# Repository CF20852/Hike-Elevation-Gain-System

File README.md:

# Hike Elevation Gain System

## :construction: Still! UNDER CONSTRUCTION :construction:
There's just another week's worth of work to do, and there always will be.
## Description
This tool uses a microcomputer connected to a GPS receiver and a barometric pressure sensor to record timestamped hike latitude, longitude, and both GPS and barometric elevation data, and a macro-enabled Excel workbook that processes the recorded data to calculate an accurate elevation gain value for a hike.  The workbook VBA macros can also generate a Keyhole Markup Language (.kml) file that can be used to plot the hike route using mapping software, and calculate the total distance of the hike and the distance from the start to various landmarks along the way.

I developed this tool mainly due to frustration with the wide range of elevation gains reported by various sources, including MapMyHike, Google Maps, Google Earth, and Global Mapper.  Google Maps and Google Earth seemed to report more elevation gain than MapMyHike, and Google Earth and Global Mapper (both of which use, or can be configured to use, the Shuttle Radar Topography Mission [SRTM] terrain elevation data) seemed to be in some agreement.

The tool is a system comprising a recording component and a processing component.  The recording component uses an [Arduino](https://www.arduino.cc/en/Guide/Introduction) (or [Arduino-like](http://wiki.microduinoinc.com/Microduino_Series)) hardware platform that incorporates a GPS receiver such as a u-Blox NEO-6M or NEO-M8N to measure and record GPS time, latitude, longitude, and elevation, and a Bosch BMP180/BMP280 temperature and pressure sensor to measure and record the barometric pressure.  For information on the Arduino platform, visit the [Arduino website](https://www.arduino.cc).  For information on the u-Blox GPS receivers, visit the [u-Blox Positioning Chips and Modules website](https://www.u-blox.com/en/positioning-chips-and-modules).  For information on the Bosch pressure sensors, visit the [Bosch Sensortec website](https://www.bosch-sensortec.com/bst/products/environmental/barometric_pressure_sensors/overview_barometricpressuresensors).

The processing component consists of a macro-enabled Excel workbook that processes the recorded data.  There are four main steps in the elevation data processing:
* Correcting the barometric altimeter data, using altimeter setting data from a local airport.  This is what aircraft pilots use to ensure that they have the correct altitude information for the local area;
* Further correcting the barometric altimeter data, using terrain elevation data, which helps remove any constant bias in the barometric elevation data;
* Filtering (smoothing) and plotting the elevation data; and 
* Computing hike elevation gain/loss statistics.

More specifically, processing the hike elevation data includes the following steps:
* Compute some basic statistics of the hike, which include:
  * Start and end time
  * Average latitude and longitude
* Get the Meteorological Terminal Aviation Routine Weather Report (METAR) data for the airport nearest the hike site from before the beginning of the hike until after the end of the hike, using an [API](https://www.aviationweather.gov/help/webservice?page=metarjson) from [NOAA's Aviation Weather Center](https://aviationweather.gov/metar) that returns data in JSON (JavaScript Object Notation) format.  This gives us the local barometric altimeter setting that aircraft pilots use to set their altimeters to indicate the correct altitude, regardless of the local barometric pressure (within reasonable limits).
* Interpolate the METAR altimeter setting data between METAR sample times for each hike data recording sample time.
* Use the interpolated altimeter setting data to correct the measured barometric-pressure-based elevation data.
* Get the Google Maps elevation data corresponding to the latitude/longitude coordinates, using a [Google Maps API](https://developers.google.com/maps/) that returns data in JSON format.  This gives us (I think) the SRTM elevation data.
* Further correct the recorded barometric elevation data by applying a 1st order correction based on the Google Maps elevation data, to correct any constant bias in the barometric pressure data.  This is done using the Excel Solver add-in to calculate a constant barometric pressure offset value that minimizes the sum of the squared differences between the barometric elevation value and the Google Maps elevation value at each hike data recording sample time.
* Filter the GPS, barometric, and Google Maps elevation data using an [infinite-impulse-response (IIR) filter](https://en.wikipedia.org/wiki/Infinite_impulse_response), the development of which has been facilitated by a [tool](http://www-users.cs.york.ac.uk/~fisher/mkfilter/trad.html) developed by Tony Fisher (who is, unfortunately, deceased).
* Compute and display the hike elevation gain and loss from GPS elevation, barometric elevation, and Google Maps elevation.
* Plot (graph) the data.

My initial findings, based on data from 4-5 hikes, are that the barometric elevation data (once calibrated) are probably more realistic and less "noisy" than the measured GPS elevation data and the Google Maps elevation data.  An additional finding, based on experiments with a counterfeit of a u-Blox NEO-6M receiver, is that some GPS receivers (such as the genuine u-Blox receiver) provide much more accurate results than others (such as the Chinese counterfeit of a u-Blox NEO-6M receiver apparently manufactured by Hangzhou ZhongKe Microelectronics CO., Ltd).

## Installation
### Arduino (like) Code
I've posted three versions of the Arduino (or Arduino-like) code.  These three versions are posted here as Arduino sketchbook (not sketch) folders.  All of them use [William Greiman's SdFat library, which can be obtained at this link](https://github.com/greiman/SdFat).  In addition, they use customized versions of [SlashDevin's NeoGPS library](https://github.com/SlashDevin/NeoGPS), which I placed in the libraries folder inside the Arduino sketchbook folder for each version:
    - A version that runs on a Microduino Core+ with the Microduino GPS, Motion, SD, and USBTTL modules, which requires you to install the Arduino for Microduino Integrated Development Environment (IDE) from [the Microduino download site](https://microduinoinc.com/download/).  This IDE includes libraries for the Microduino Motion (\_06_m_Module_Motion), module, which I use, and GPS module (\_06_m_Module_GPS), which I don't use, except for testing the hardware configuration.  For the GPS receiver, I use SlashDevin's NeoGPS library, with some customization in the header files.  Please refer to the NEO-6M Setup.docx document for explanation of the customization.  The Core+ gives you two hardware serial ports.
    - A version that runs on an Arduino Uno with a shield containing a Chinese counterfeit of a u-Blox NEO-6M GPS receiver, which does not implement the u-Blox protocol, and a microSD card socket, and an [Adafruit BMP280 Barometric Pressure + Temperature Sensor Breakout](https://learn.adafruit.com/adafruit-bmp280-barometric-pressure-plus-temperature-sensor-breakout) that I attached and wired onto the shield, connecting SDA on the BMP280 breakout to A4 (SDA) on the Arduino and SCL on the BMP280 breakout to A5 (SCL) on the Arduino.  For this version, I have used SlashDevin's NeoGPS library with some customization in the header files, and the Adafruit BMP280 library.  I found a Chinese-language protocol specification for the Chinese GPS module labeled as a u-blox NEO-6M at [Hangzhou Zhongke Microelectronics Co., Ltd.](http://www.icofchina.com/d/file/xiazai/2017-05-02/ea0cdd3d81eeebcc657b5dbca80925ee.pdf) and translated it to English (with some expected formatting issues) using an [online document translator](https://www.onlinedoctranslator.com/en/translate-chinese-(simplified)-to-english_zh-CN_en), which worked better than expected.  I put a copy of the translated document in the sketchbook folder for this version.  The Arduino Uno only gives you one hardware serial port, tied to the USB port, so this version uses SlashDevin's NeoSWSerial library to communicate with the GPS module.
    - A version that runs on an Arduino Uno with a [DuinoPeak shield](http://duinopeak.com/index.php?route=product/product&product_id=112) containing a u-Blox NEO-N8M GPS receiver and a microSD card socket, and an [Adafruit BMP280 Barometric Pressure + Temperature Sensor Breakout](https://learn.adafruit.com/adafruit-bmp280-barometric-pressure-plus-temperature-sensor-breakout) that I attached and wired onto the shield, connecting SDA on the BMP280 breakout to A4 (SDA) on the Arduino and SCL on the BMP280 breakout to A5 (SCL) on the Arduino.  I used SlashDevin's NeoGPS library with customized header files and the Adafruit BMP280 library for this version also.
1.  Configure your hardware according to one of the options above.
2.  Download the corresponding sketchbook folder.
3.  In the Arduino IDE, go to File... Preferences... Sketchbook location and set the sketchbook location to the location of the sketchbook folder corresponding to the hardware configuration you chose.  See the notes on Arduino library usage below for an explanation of why I do it this way.
4.  Compile and upload the sketch to your Arduino or Microduino.
#### Some notes on Arduino library usage
When I first started developing the three hardware variants of this project, I put all of the necessary libraries in C:\Users\username\My Documents\Arduino\libraries, where my sketchbook folder was C:\Users\username\My Documents\Arduino.  That was OK for the barometric pressure sensor, because I could use one library for the BMP180 and another library for the BMP280, with no customization required.  But the NeoGPS library is highly configurable via multiple header files for different protocol types (e.g., NMEA vs proprietary), variations on what NMEA sentences different receivers put out, and what information you want out of those sentences (e.g., if you don't need speed and heading, you can configure the library to not parse them, thus saving processing time and memory).  The NeoGPS library has a a src folder containing NMEA sentence processing .h and .cpp files, and subfolder under src called ublox, which contains .h and .cpp files for handling the u-blox proprietary GPS receiver protocol.  In addition, using an Arduino Uno, which only has one hardware serial port, you have a specific GPS serial port configuration, but with the Microduino Core+, you have a second hardware serial port that you can use, which requires a different GPSPort.h configuration in NeoGPS.  So I started out creating different versions of the various NeoGPS header files with different names for the different configurations.  This (IMO) was a really bad idea, because if I update the NeoGPS library, the Arduino library manager replaces the existing library folder with the updated library folder, thus wiping out any custom header files I created.  (Hooray for daily backups!)  Moreover, it starts to get ugly (inelegant) fast.

After some research, I learned that the Arduino IDE looks for libraries in several places (the following is Windows specific):  (1) the libraries folder in your sketchbook, e.g. C:\Users\username\My Documents\Arduino\libraries; (2) in the libraries folder of the Arduino IDE installation folder, e.g. C:\Program Files (x86)\Arduino\libraries; (3) in the folders below C:\Program Files (x86)\Arduino\hardware, e.g., C:\Program Files (x86)\Arduino\hardware\arduino\avr\libraries; and (4) in your sketch folder.  If you want to include a library in one of the first three places, you enclose the appropriate header file name in angle brackets (<>), e.g.,

`#include <SomeLib.h>`,

and if you want to include a library in your sketch (not sketchbook) folder, you enclose the header file name in double quotes, e.g.

`#include "MyLib.h"`.

I'm told that if you use the latter syntax, if the Arduino IDE doesn't find the library source file in your sketch folder, it will look in the places listed above for the angle bracket syntax.

To be able to have several different configurations of the NeoGPS library, as well as other libraries including Adafruit_BMP280_Library or Adafruit_BMP085_Library, NeoSWSerial (if using an Arduino Uno, not needed for a Microduino Core+), PString, and SDFat, the solution I eventually settled on is to have a different sketchbook folder for each configuration, containing a libraries folder and a sketch folder.  I have a copy of the each of the required libraries that are normally stored in the Arduino sketchbook folder in the libraries folder of the hardware-configuration-specific sketchbook folders.  The main disadvantage of this approach (in addition to multiple copies of libraries that you may need to update) is that you have to remember to point the Arduino IDE to the correct sketchbook.  You can easily change the sketchbook folder that the Arduino IDE uses under File... Preferences... Sketchbook location in the Arduino IDE (I'm using version 1.8.5 right now).

Another thing I learned is that if a library has at least one subfolder containing additional source code (.h and/or .cpp) files, all of the source code files must be within a src folder inside the library folder, or the IDE won't find the source code files within the subfolder.  An exception to this src folder requirement may be if the subfolder is named "utility".  See the Arduino IDE 1.5: Library specfication, under the Layout of folders and files heading.  I quote:  

>The source code found in src folder and all its subfolders is compiled and linked in the user's sketch. Only the src folder is added to the include search path (both when compiling the sketch and the library). When the user imports a library into their sketch (from the "Tools > Import Library" menu), an #include statement will be added for all header (.h) files in the src/ directory (but not its subfolders). As a result, these header files form something of a de facto interface to your library; in general, the only header files in the root src/ folder should be those that you want to expose to the user's sketch and plan to maintain compatibility with in future versions of the library. Place internal header files in a subfolder of the src/ folder.

>For backward compatibility with Arduino 1.0.x, the library author may opt to place source code into the root folder, instead of the folder called src. In this case the 1.0 library format is applied and the source code is searched from the library root folder and the utility folder...

I hope this explanation helps someone avoid wasting the amount of time I did in making my project work and look (I hope) at least a bit elegant.

### Excel Workbook
1.  Of course, you'll need Microsoft Excel to use the Excel macro-enabled workbook.  I used Excel 2016.

2.  I was very happy to find an Excel Visual Basic for Applications (VBA) JSON parser at https://github.com/VBA-tools/VBA-JSON.  It's always nice to find some giants who are willing to let you stand on their shoulders.  I just downloaded JsonConverter.bas from [that site](https://github.com/VBA-tools/VBA-JSON) and imported it into my Visual Basic code as a module.

3.  My Excel macro-enabled workbook also uses the Solver Add-in.  If you haven't already enabled it in your copy of Excel, you'll need to do so.  In my version (2016) of Excel, that's done by going to File... Options... Add-ins... Manage Excel Add-ins... Go, and then checking the Solver box and clicking OK.  Depending on which version of Excel you have, your approach may differ.

4.  Download and open the workbook from this page.  When you open the spreadsheet in Excel, you'll probably have to OK enabling macros.

5.  I hike mainly in Arizona, Maryland, Pennsylvania, Virginia, and West Virginia, so those are the states for which I've included airports that report METAR data in the Airports tab of the workbook.  If you live somewhere else, you'll need to download the airports for your area from the [ADDS Station Table](https://www.aviationweather.gov/docs/metar/stations.txt).  Only include the stations that have a "X" in the "M" column of the table (column 63).  Just append them to the bottom of the Airports sheet below the other airports.

## Operation
### Arduino
There's not much to it.  The way it stands right now, if you plug a [well-formatted SD card](https://www.sdcard.org/downloads/formatter_4/) into the recorder, with less than 99 HikeLgxx.csv files (where xx = 0-99) on it, and apply power, it'll create a new HikeLgxx.csv file with the next available number and start recording every 2 seconds as soon as the GPS receiver starts outputting messages.
### Excel Workbook
#### Elevation Gain Calculations
This is a lot more complicated than the Arduino part, given the current state of the "art"...
1.  Ensure that you have an internet connection, because the macros have to retrieve data using the Aviation Weather Center METAR API and the Google Maps elevation data API;
2.  On the Control sheet of the Excel workbook, enter the following data:
    - Your Google Maps API key, which you can obtain from [this website](https://developers.google.com/maps/documentation/elevation/start), in cell B7;
    - Date of the hike, in YYYY-MM-DD or MM/DD/YYYY format, in cell B14.
    - As far as the other cells on the Control sheet are concerned, you should either not mess with them or they will be automagically filled in by the macros.
2.  Open the .csv file recorded by the Microduino or Arduino as an Excel spreadsheet;
3.  Delete everything in the Data sheet of the Excel workbook below the header row, which is row 1 i.e., delete everything in row 2 and below;
4.  Copy the UTC time, latitude and longitude (+/-DD.DDDDD format), GPS elevation (feet), temperature (degrees C), pressure (HPa), baro elevation (feet), number of satellites, HDOP, and VDOP data from the appropriate Hikelgxx.csv file to the Data sheet starting in Row 2, Column 1, i.e. starting in cell A2 of the Data worksheet;
5.  Press \<CTRL>\<p>  to start processing the data.
6.  Look at the results on the Data sheet, primarily in Row 2, Columns U, Y, and AC.  Also look at the two charts, Unfilt Elev and Filt Elev, to get a sense of how the three data sources (GPS elevation, baro elevation, and Google Maps elevation) match up.
#### KML File Generation
This is somewhat simpler than the elevation gain calculations:
1.  On the Control sheet of the Excel workbook, enter the file location at which you want to store your .kml file, should you choose to generate one, in cells B1-B3;
2.  Press \<CTRL>\<k> to generate the .kml file.
#### Distance Calculations
##### Total Hike Distance Calculation
Press \<CTRL>\<d> to calculate the total distance of the hike.
##### Distance to a Waypoint or Landmark
1. Enter the latitude and longitude of the waypoint in cells B27 and C27 respectively;
2. Press \<CTRL>\<q> to calculate the distance.

##  Brief Description of the Excel Workbook
### Control Tab
This is the worksheet on which you enter some parameters related to generating a Keyhole Markup Language (.kml) file, your Google Maps API keyt, the date of the hike, waypoint latitude and longitude if you want to calculate distance to a waypoint.  It's also where certain intermediate results of the elevation processing show up, and where the distances are displayed.
### Data Tab
This is the worksheet onto which you copy and paste the data from the hike log file recorded by the Arduino (like) machine.
### Airports Tab
This is the worksheet that contains the information (most importantly, the latitude and longitude) of any airports from which you want the workbook to retrieve local altimeter setting data.
### METARS Tab
This is a worksheet whose contents are automatically generated by the macros after retrieving the METAR data for the selected airport.
### GM API Rqsts Tab
This is a worksheet whose contents are automatically generated by the macros in the process of requesting elevation data from Google Maps.
### GM Elev Tab
This is a worksheet whose contents are automatically generated by the macros from the elevation data returned by the Google Maps API.
### Unfilt Elev Chart
This is an automatically generated chart showing the unfiltered barometric, GPS, and Google Maps elevation data versus UTC time.
### Filt Elev Chart
This is an automatically generated chart showing the filtered barometric, GPS, and Google Maps elevation data versus UTC time.  The filter is a digital third-order Butterworth IIR filter implemented in a macro.
### Filt Elev v Dist Chart
This is an automatically generated chart showing the filtered barometric, GPS, and Google Maps elevation data versus distance from the beginning of the hike.  The filter is a digital third-order Butterworth IIR filter implemented in a macro.

## Some initial results
This figure shows the GPS altitude (blue) and barometric cabin pressure (orange) of a flight from Phoenix, Arizona to Baltimore, Maryland, just plotted straight from the recorded .csv file:

This figure shows the GPS altitude and corrected barometric elevation measured at a stationary location next to a sliding glass door in my basement, processed through the Excel workbook:

This figure shows the filtered GPS, barometric, and Google Maps elevations with respect to distance from the beginning of a hike from where the Appalachian Trail crosses State Rte 94 south of Mount Holly Springs, Pennsylvania to Boiling Springs, Pennsylvania.  This used a u-blox NEO-M8N GNSS receiver, which I think I accidently left in AIR_4G dynamics mode, instead of PEDESTRIAN mode:

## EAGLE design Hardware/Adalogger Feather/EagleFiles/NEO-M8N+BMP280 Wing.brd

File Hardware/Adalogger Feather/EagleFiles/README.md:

Autodesk Eagle 9.0.1 (free version) files for a Feather daughterboard for an Adafruit Feather M0 Adalogger.

There is at least one error in this design:  the GPIOSDA and GPIOSCL lines coming from the Adafruit Adalogger board do not have pullup resistors, and because these lines are open-drain, the daughterboard must provide the pullup resistors.

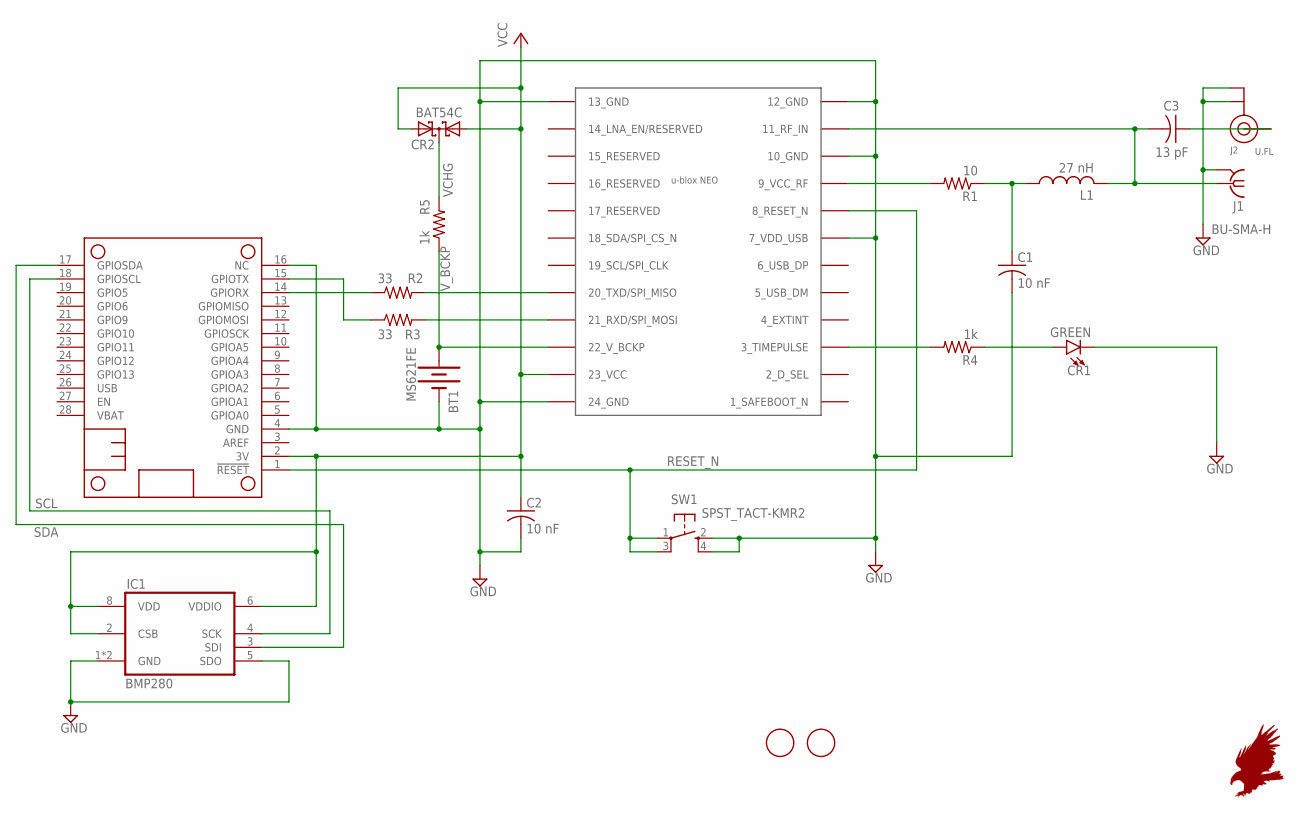
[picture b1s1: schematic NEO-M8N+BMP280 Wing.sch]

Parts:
BT1: MS621FE; BATTCON-6.8MM
C1, C2: 10 nF; C0402
C3: 13 pF; C0402
CR1: GREEN; LED-0603
CR2: BAT54C; SOT23
FID1, FID2: FIDUCIAL; FIDUCIAL_1MM
IC1: BMP280
J1: BU-SMA-H
J2: U.FL
L1: 27 nH; L0402
MS1: FEATHERWING
R1: 10; R0805
R2, R3: 33; R0805
R4, R5: 1k; R0805
SW1: SPST_TACT-KMR2; KMR2
U$2: NEO-M8

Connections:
FEATHER_RXD: MS1.14 (GPIORX), R2.1
FEATHER_TXD: MS1.15 (GPIOTX), R3.1
GND: BT1.-, C1.2, C2.2, CR1.C, IC1.1 (GND), IC1.5 (SDO), IC1.7 (GND), J1.2, J1.3 (2), J1.4 (2), J1.5 (2), J2.1 (GND), J2.2 (GND), MS1.4 (GND), MS1.16 (NC), SW1.2 (S), SW1.4 (S1), U$2.7 (7_VDD_USB), U$2.10 (10_GND), U$2.12 (12_GND), U$2.13 (13_GND), U$2.24 (24_GND)
GPS_RXD: R3.2, U$2.21 (21_RXD/SPI_MOSI)
GPS_TXD: R2.2, U$2.20 (20_TXD/SPI_MISO)
J2_RF: C3.1, J2.3 (SIGNAL)
LED_ANODE: CR1.A, R4.1
LNA_BIAS: C1.1, L1.P$1 (1), R1.1
RESET_N: MS1.1 (!RESET), SW1.1, SW1.3 (P1), U$2.8 (8_RESET_N)
RF_IN: C3.2, J1.1, L1.P$2 (2), U$2.11 (11_RF_IN)
SCL: IC1.4 (SCK), MS1.18 (GPIOSCL)
SDA: IC1.3 (SDI), MS1.17 (GPIOSDA)
TP: R4.2, U$2.3 (3_TIMEPULSE)
VCC: C2.1, CR2.1 (A1), CR2.2 (A2), IC1.2 (CSB), IC1.6 (VDDIO), IC1.8 (VDD), MS1.2 (3V), U$2.23 (23_VCC)
VCC_RF: R1.2, U$2.9 (9_VCC_RF)
VCHG: CR2.3 (CC), R5.2
V_BCKP: BT1.+, R5.1, U$2.22 (22_V_BCKP)

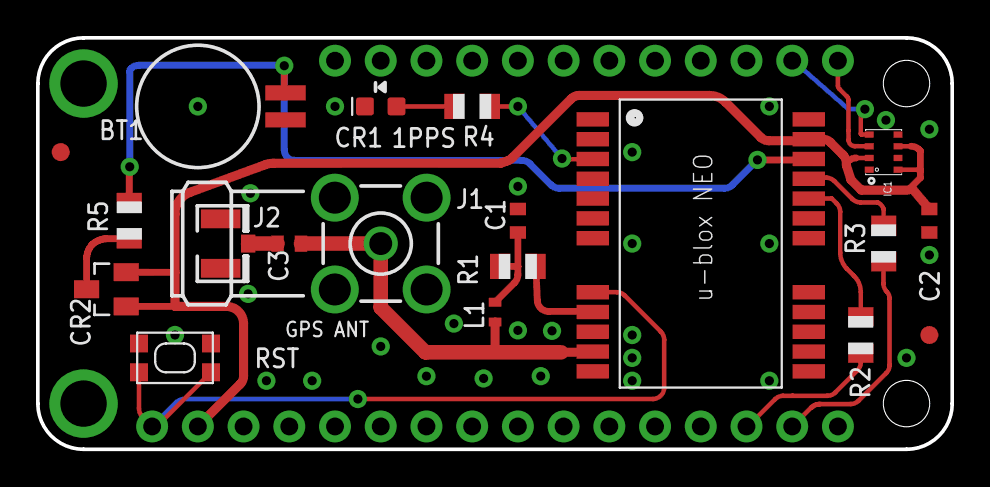
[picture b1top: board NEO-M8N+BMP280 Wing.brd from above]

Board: 2 copper layers, 50.8 x 22.9 mm, 20 parts (0 on the bottom side), 17 nets.

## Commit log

2018-05-22 Bug fix and enhancements
2018-06-02 Added Adafruit Adalogger version; added date & timestamp to file
2018-07-06 Update to disclose design error

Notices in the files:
Hardware/Adalogger Feather/EagleFiles/NEO-M8N+BMP280 Wing.brd:
(c) 2018 Spectrum Applications
parts and their libraries:
SparkFun-LED: Licensing: Creative Commons ShareAlike 4.0 International - https://creativecommons.org/licenses/by-sa/4.0
